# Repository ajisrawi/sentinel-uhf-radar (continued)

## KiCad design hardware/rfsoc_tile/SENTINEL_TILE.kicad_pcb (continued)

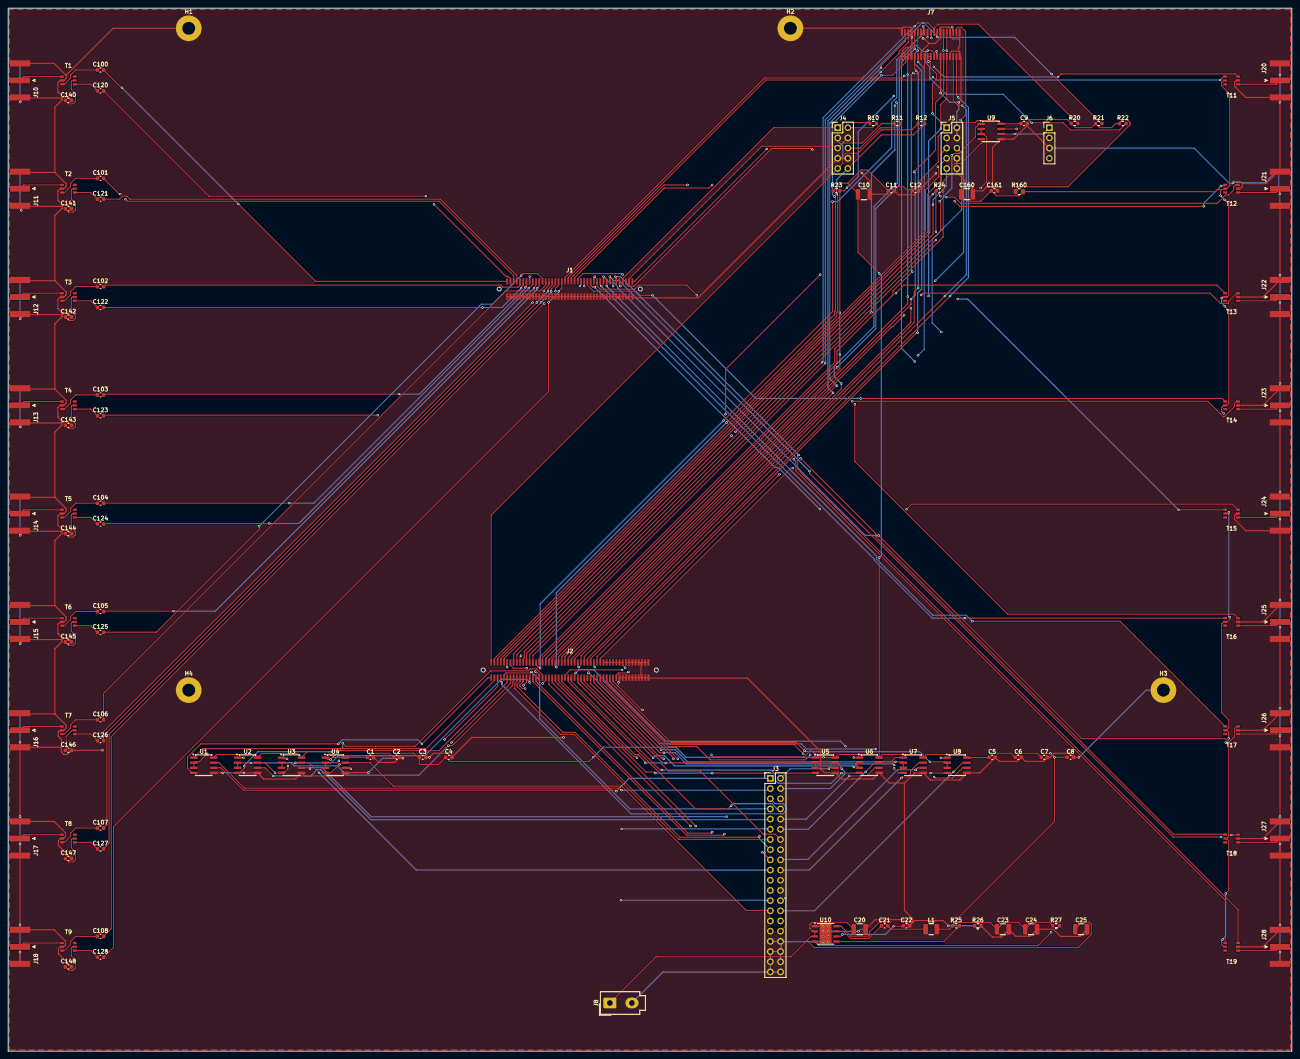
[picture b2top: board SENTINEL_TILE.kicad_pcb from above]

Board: 4 copper layers, 320.0 x 260.0 mm, 118 parts (0 on the bottom side), 187 nets.

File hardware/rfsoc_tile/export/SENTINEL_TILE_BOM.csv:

"Item","References","Qty","Value","Footprint","Description","MPN / part class"
"1","C1-C9,C11,C12,C21,C100-C108,C120-C128,C140-C148,C161","40","100n","Capacitor_SMD:C_0603_1608Metric","Centre-tap AC ground",""
"2","C10,C160","2","10u","Capacitor_SMD:C_1210_3225Metric","QSFP supply filter",""
"3","C20","1","10u 25V","Capacitor_SMD:C_1210_3225Metric","",""
"4","C22","1","1u","Capacitor_SMD:C_0603_1608Metric","",""
"5","C23,C24","2","22u","Capacitor_SMD:C_1210_3225Metric","",""
"6","C25","1","22u 25V","Capacitor_SMD:C_1210_3225Metric","",""
"7","H1-H4","4","M3","MountingHole:MountingHole_3.2mm_M3_Pad","",""
"8","J1","1","SOM CONN A","SENTINEL:SOM_B2B_2x40_P0.8","SOM data-converter connector",""
"9","J2","1","SOM CONN B","SENTINEL:SOM_B2B_2x50_P0.8","SOM control / optics / power connector",""
"10","J3","1","BACKPLANE","Connector_PinHeader_2.54mm:PinHeader_2x20_P2.54mm_Vertical","Cable to tile backplane J9 (pin-for-pin)",""
"11","J4","1","CLOCK","Connector_PinHeader_2.54mm:PinHeader_2x05_P2.54mm_Vertical","From clock board",""
"12","J5","1","CAL CTRL","Connector_PinHeader_2.54mm:PinHeader_2x05_P2.54mm_Vertical","To calibration board J11",""
"13","J6","1","PSU LINK","Connector_PinHeader_2.54mm:PinHeader_1x04_P2.54mm_Vertical","",""
"14","J7","1","QSFP28","SENTINEL:QSFP28_Host_38P","QSFP28 to face beamformer, 4 x 25 Gb/s",""
"15","J8","1","12V IN","Connector_Molex:Molex_Mini-Fit_Jr_5566-02A_2x01_P4.20mm_Vertical","12 V from subarray PSU aux, 4 A",""
"16","J10","1","RX1","Connector_Coaxial:SMA_Amphenol_132289_EdgeMount","From T/R module 1 RX_OUT",""
"17","J11","1","RX2","Connector_Coaxial:SMA_Amphenol_132289_EdgeMount","From T/R module 2 RX_OUT",""
"18","J12","1","RX3","Connector_Coaxial:SMA_Amphenol_132289_EdgeMount","From T/R module 3 RX_OUT",""
"19","J13","1","RX4","Connector_Coaxial:SMA_Amphenol_132289_EdgeMount","From T/R module 4 RX_OUT",""
"20","J14","1","RX5","Connector_Coaxial:SMA_Amphenol_132289_EdgeMount","From T/R module 5 RX_OUT",""
"21","J15","1","RX6","Connector_Coaxial:SMA_Amphenol_132289_EdgeMount","From T/R module 6 RX_OUT",""
"22","J16","1","RX7","Connector_Coaxial:SMA_Amphenol_132289_EdgeMount","From T/R module 7 RX_OUT",""
"23","J17","1","RX8","Connector_Coaxial:SMA_Amphenol_132289_EdgeMount","From T/R module 8 RX_OUT",""
"24","J18","1","RXCAL","Connector_Coaxial:SMA_Amphenol_132289_EdgeMount","From calibration board MEASURE",""
"25","J20","1","TX1","Connector_Coaxial:SMA_Amphenol_132289_EdgeMount","To T/R module 1 TX_IN",""
"26","J21","1","TX2","Connector_Coaxial:SMA_Amphenol_132289_EdgeMount","To T/R module 2 TX_IN",""
"27","J22","1","TX3","Connector_Coaxial:SMA_Amphenol_132289_EdgeMount","To T/R module 3 TX_IN",""
"28","J23","1","TX4","Connector_Coaxial:SMA_Amphenol_132289_EdgeMount","To T/R module 4 TX_IN",""
"29","J24","1","TX5","Connector_Coaxial:SMA_Amphenol_132289_EdgeMount","To T/R module 5 TX_IN",""
"30","J25","1","TX6","Connector_Coaxial:SMA_Amphenol_132289_EdgeMount","To T/R module 6 TX_IN",""
"31","J26","1","TX7","Connector_Coaxial:SMA_Amphenol_132289_EdgeMount","To T/R module 7 TX_IN",""
"32","J27","1","TX8","Connector_Coaxial:SMA_Amphenol_132289_EdgeMount","To T/R module 8 TX_IN",""
"33","J28","1","TXCAL","Connector_Coaxial:SMA_Amphenol_132289_EdgeMount","To calibration board INJECT",""
"34","L1","1","4.7u","Inductor_SMD:L_1210_3225Metric","",""
"35","R10-R12,R24","4","100","Resistor_SMD:R_0603_1608Metric","LVDS receiver termination,LVDS termination (DNP if SOM terminates),MGT reference clock termination (refclk from SOM oscillator)",""
"36","R20-R23","4","4.7k","Resistor_SMD:R_0603_1608Metric","",""
"37","R25,R27","2","100k","Resistor_SMD:R_0603_1608Metric","",""
"38","R26","1","43.2k","Resistor_SMD:R_0603_1608Metric","",""
"39","R160","1","0","Resistor_SMD:R_0805_2012Metric","DAC_AVTT from 3.3 V (fit per SOM DAC mode: 2.5 V or 3.0 V)",""
"40","T1-T9,T11-T19","18","1:2","SENTINEL:Balun_SMD_6P_3.8x3.8","ADC input transformer, 50 -> 100 ohm,DAC output transformer, centre tap biases the DAC",""
"41","U1-U9","9","THVD1450","Package_SO:SOIC-8_3.9x4.9mm_P1.27mm","RS-485 to T/R module 1,RS-485 to T/R module 2,RS-485 to T/R module 3,RS-485 to T/R module 4,RS-485 to T/R module 5,RS-485 to T/R module 6,RS-485 to T/R module 7,RS-485 to T/R module 8,RS-485 to subarray PSU",""
"42","U10","1","LMR33630","Package_SO:Texas_HSOP-8-1EP_3.9x4.9mm_P1.27mm_ThermalVias","12 V -> 3.3 V, 3 A",""

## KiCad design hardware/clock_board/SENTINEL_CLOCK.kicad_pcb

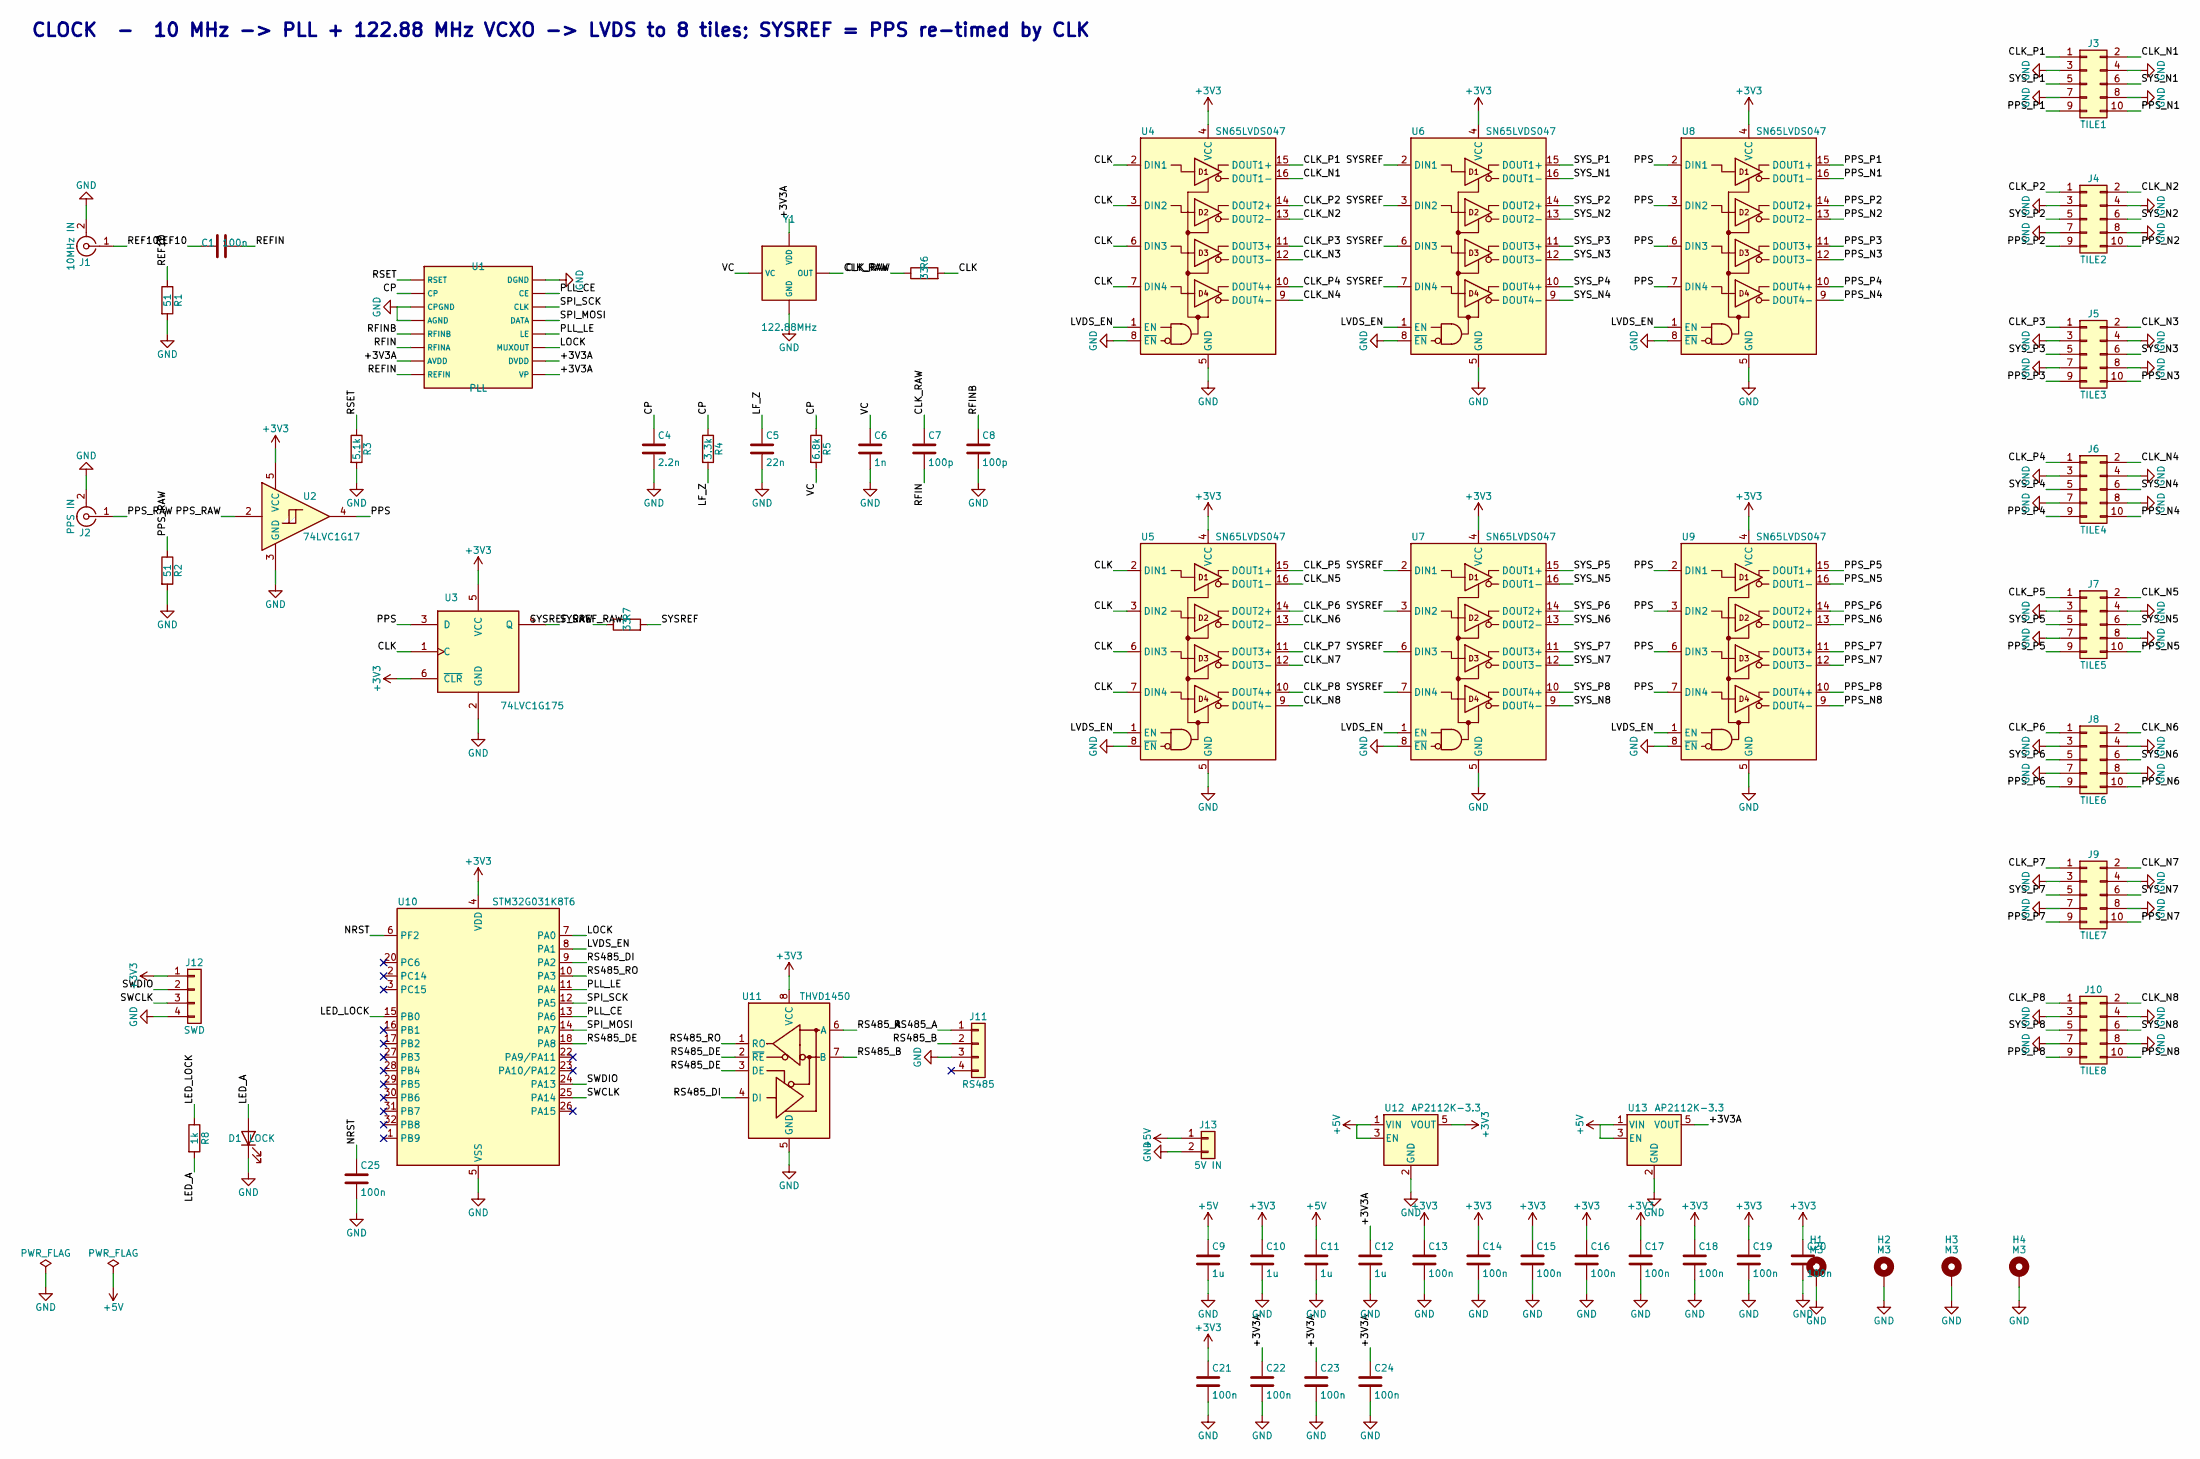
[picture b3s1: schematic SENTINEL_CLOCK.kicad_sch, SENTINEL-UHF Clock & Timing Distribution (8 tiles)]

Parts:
C1, C13, C14, C15, C16, C17, C18, C19, C20, C21, C22, C23, C24, C25: 100n; C_0603_1608Metric
C4: 2.2n; C_0603_1608Metric
C5: 22n; C_0603_1608Metric
C6: 1n; C_0603_1608Metric
C7, C8: 100p; C_0603_1608Metric
C9, C10, C11, C12: 1u; C_0603_1608Metric
D1: LOCK; LED_0603_1608Metric
H1, H2, H3, H4: M3; MountingHole_3.2mm_M3_Pad
J1: 10MHz IN; SMA_Amphenol_132289_EdgeMount
J2: PPS IN; SMA_Amphenol_132289_EdgeMount
J3: TILE1; PinHeader_2x05_P2.54mm_Vertical
J4: TILE2; PinHeader_2x05_P2.54mm_Vertical
J5: TILE3; PinHeader_2x05_P2.54mm_Vertical
J6: TILE4; PinHeader_2x05_P2.54mm_Vertical
J7: TILE5; PinHeader_2x05_P2.54mm_Vertical
J8: TILE6; PinHeader_2x05_P2.54mm_Vertical
J9: TILE7; PinHeader_2x05_P2.54mm_Vertical
J10: TILE8; PinHeader_2x05_P2.54mm_Vertical
J11: RS485; PinHeader_1x04_P2.54mm_Vertical
J12: SWD; PinHeader_1x04_P2.54mm_Vertical
J13: 5V IN; Molex_Mini-Fit_Jr_5566-02A_2x01_P4.20mm_Vertical
R1, R2: 51; R_0603_1608Metric
R3: 5.1k; R_0603_1608Metric
R4: 3.3k; R_0603_1608Metric
R5: 6.8k; R_0603_1608Metric
R6, R7: 33; R_0603_1608Metric
R8: 1k; R_0603_1608Metric
U1: PLL; TSSOP-16_4.4x5mm_P0.65mm
U2: 74LVC1G17; SOT-23-5
U3: 74LVC1G175; SOT-363_SC-70-6
U4, U5, U6, U7, U8, U9: SN65LVDS047; SOIC-16_3.9x9.9mm_P1.27mm
U10: STM32G031K8T6; LQFP-32_7x7mm_P0.8mm
U11: THVD1450; SOIC-8_3.9x4.9mm_P1.27mm
U12, U13: AP2112K-3.3; SOT-23-5
Y1: 122.88MHz; Oscillator_SMD_EuroQuartz_XO53-4Pin_5.0x3.2mm

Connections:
+3V3: C10.1, C13.1, C14.1, C15.1, C16.1, C17.1, C18.1, C19.1, C20.1, C21.1, J12.1, U2.5 (VCC), U3.5 (VCC), U3.6 (~CLR), U4.4 (VCC), U5.4 (VCC), U6.4 (VCC), U7.4 (VCC), U8.4 (VCC), U9.4 (VCC), U10.4 (VDD), U11.8 (VCC), U12.5 (VOUT)
+3V3A: C12.1, C22.1, C23.1, C24.1, U1.7 (AVDD), U1.15 (DVDD), U1.16 (VP), U13.5 (VOUT), Y1.4 (VDD)
+5V: C9.1, C11.1, J13.1, U12.1 (VIN), U12.3 (EN), U13.1 (VIN), U13.3 (EN)
CLK: R6.2, U3.1 (C), U4.2 (DIN1), U4.3 (DIN2), U4.6 (DIN3), U4.7 (DIN4), U5.2 (DIN1), U5.3 (DIN2), U5.6 (DIN3), U5.7 (DIN4)
CLK_N1: J3.2, U4.16 (DOUT1-)
CLK_N2: J4.2, U4.13 (DOUT2-)
CLK_N3: J5.2, U4.12 (DOUT3-)
CLK_N4: J6.2, U4.9 (DOUT4-)
CLK_N5: J7.2, U5.16 (DOUT1-)
CLK_N6: J8.2, U5.13 (DOUT2-)
CLK_N7: J9.2, U5.12 (DOUT3-)
CLK_N8: J10.2, U5.9 (DOUT4-)
CLK_P1: J3.1, U4.15 (DOUT1+)
CLK_P2: J4.1, U4.14 (DOUT2+)
CLK_P3: J5.1, U4.11 (DOUT3+)
CLK_P4: J6.1, U4.10 (DOUT4+)
CLK_P5: J7.1, U5.15 (DOUT1+)
CLK_P6: J8.1, U5.14 (DOUT2+)
CLK_P7: J9.1, U5.11 (DOUT3+)
CLK_P8: J10.1, U5.10 (DOUT4+)
CLK_RAW: C7.1, R6.1, Y1.3 (OUT)
CP: C4.1, R4.1, R5.1, U1.2 (CP)
GND: C4.2, C5.2, C6.2, C8.2, C9.2, C10.2, C11.2, C12.2, C13.2, C14.2, C15.2, C16.2, C17.2, C18.2, C19.2, C20.2, C21.2, C22.2, C23.2, C24.2, C25.2, D1.1 (K), H1.1, H2.1, H3.1, H4.1, J1.2 (Ext), J2.2 (Ext), J3.3, J3.4, J3.7, J3.8, J4.3, J4.4, J4.7, J4.8, J5.3, J5.4, J5.7, J5.8, J6.3, J6.4, J6.7, J6.8, J7.3, J7.4, J7.7, J7.8, J8.3, J8.4, J8.7, J8.8, J9.3, J9.4, J9.7, J9.8, J10.3, J10.4, J10.7, J10.8, J11.3, J12.4, J13.2, R1.2, R2.2, R3.2, U1.3 (CPGND), U1.4 (AGND), U1.9 (DGND), U2.3 (GND), U3.2 (GND), U4.5 (GND), U4.8 (~EN), U5.5 (GND), U5.8 (~EN), U6.5 (GND), U6.8 (~EN), U7.5 (GND), U7.8 (~EN), U8.5 (GND), U8.8 (~EN), U9.5 (GND), U9.8 (~EN), U10.5 (VSS), U11.5 (GND), U12.2 (GND), U13.2 (GND), Y1.2 (GND)
LED_A: D1.2 (A), R8.2
LED_LOCK: R8.1, U10.15 (PB0)
LF_Z: C5.1, R4.2
LOCK: U1.14 (MUXOUT), U10.7 (PA0)
LVDS_EN: U4.1 (EN), U5.1 (EN), U6.1 (EN), U7.1 (EN), U8.1 (EN), U9.1 (EN), U10.8 (PA1)
NRST: C25.1, U10.6 (PF2)
PLL_CE: U1.10 (CE), U10.13 (PA6)
PLL_LE: U1.13 (LE), U10.11 (PA4)
PPS: U2.4, U3.3 (D), U8.2 (DIN1), U8.3 (DIN2), U8.6 (DIN3), U8.7 (DIN4), U9.2 (DIN1), U9.3 (DIN2), U9.6 (DIN3), U9.7 (DIN4)
PPS_N1: J3.10, U8.16 (DOUT1-)
PPS_N2: J4.10, U8.13 (DOUT2-)
PPS_N3: J5.10, U8.12 (DOUT3-)
PPS_N4: J6.10, U8.9 (DOUT4-)
PPS_N5: J7.10, U9.16 (DOUT1-)
PPS_N6: J8.10, U9.13 (DOUT2-)
PPS_N7: J9.10, U9.12 (DOUT3-)
PPS_N8: J10.10, U9.9 (DOUT4-)
PPS_P1: J3.9, U8.15 (DOUT1+)
PPS_P2: J4.9, U8.14 (DOUT2+)
PPS_P3: J5.9, U8.11 (DOUT3+)
PPS_P4: J6.9, U8.10 (DOUT4+)
PPS_P5: J7.9, U9.15 (DOUT1+)
PPS_P6: J8.9, U9.14 (DOUT2+)
PPS_P7: J9.9, U9.11 (DOUT3+)
PPS_P8: J10.9, U9.10 (DOUT4+)
PPS_RAW: J2.1 (In), R2.1, U2.2
REF10: C1.1, J1.1 (In), R1.1
REFIN: C1.2, U1.8 (REFIN)
RFIN: C7.2, U1.6 (RFINA)
RFINB: C8.1, U1.5 (RFINB)
RS485_A: J11.1, U11.6 (A)
RS485_B: J11.2, U11.7 (B)
RS485_DE: U10.18 (PA8), U11.2 (~RE), U11.3 (DE)
RS485_DI: U10.9 (PA2), U11.4 (DI)
RS485_RO: U10.10 (PA3), U11.1 (RO)
RSET: R3.1, U1.1 (RSET)
SPI_MOSI: U1.12 (DATA), U10.14 (PA7)
SPI_SCK: U1.11 (CLK), U10.12 (PA5)
SWCLK: J12.3, U10.25 (PA14)
SWDIO: J12.2, U10.24 (PA13)
SYSREF: R7.2, U6.2 (DIN1), U6.3 (DIN2), U6.6 (DIN3), U6.7 (DIN4), U7.2 (DIN1), U7.3 (DIN2), U7.6 (DIN3), U7.7 (DIN4)
SYSREF_RAW: R7.1, U3.4 (Q)
SYS_N1: J3.6, U6.16 (DOUT1-)
SYS_N2: J4.6, U6.13 (DOUT2-)
SYS_N3: J5.6, U6.12 (DOUT3-)
SYS_N4: J6.6, U6.9 (DOUT4-)
SYS_N5: J7.6, U7.16 (DOUT1-)
SYS_N6: J8.6, U7.13 (DOUT2-)
SYS_N7: J9.6, U7.12 (DOUT3-)
SYS_N8: J10.6, U7.9 (DOUT4-)
SYS_P1: J3.5, U6.15 (DOUT1+)
SYS_P2: J4.5, U6.14 (DOUT2+)
SYS_P3: J5.5, U6.11 (DOUT3+)
SYS_P4: J6.5, U6.10 (DOUT4+)
SYS_P5: J7.5, U7.15 (DOUT1+)
SYS_P6: J8.5, U7.14 (DOUT2+)
SYS_P7: J9.5, U7.11 (DOUT3+)
SYS_P8: J10.5, U7.10 (DOUT4+)
VC: C6.1, R5.2, Y1.1 (VC)

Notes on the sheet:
CLOCK - 10 MHz -> PLL + 122.88 MHz VCXO -> LVDS to 8 tiles; SYSREF = PPS re-timed by CLK

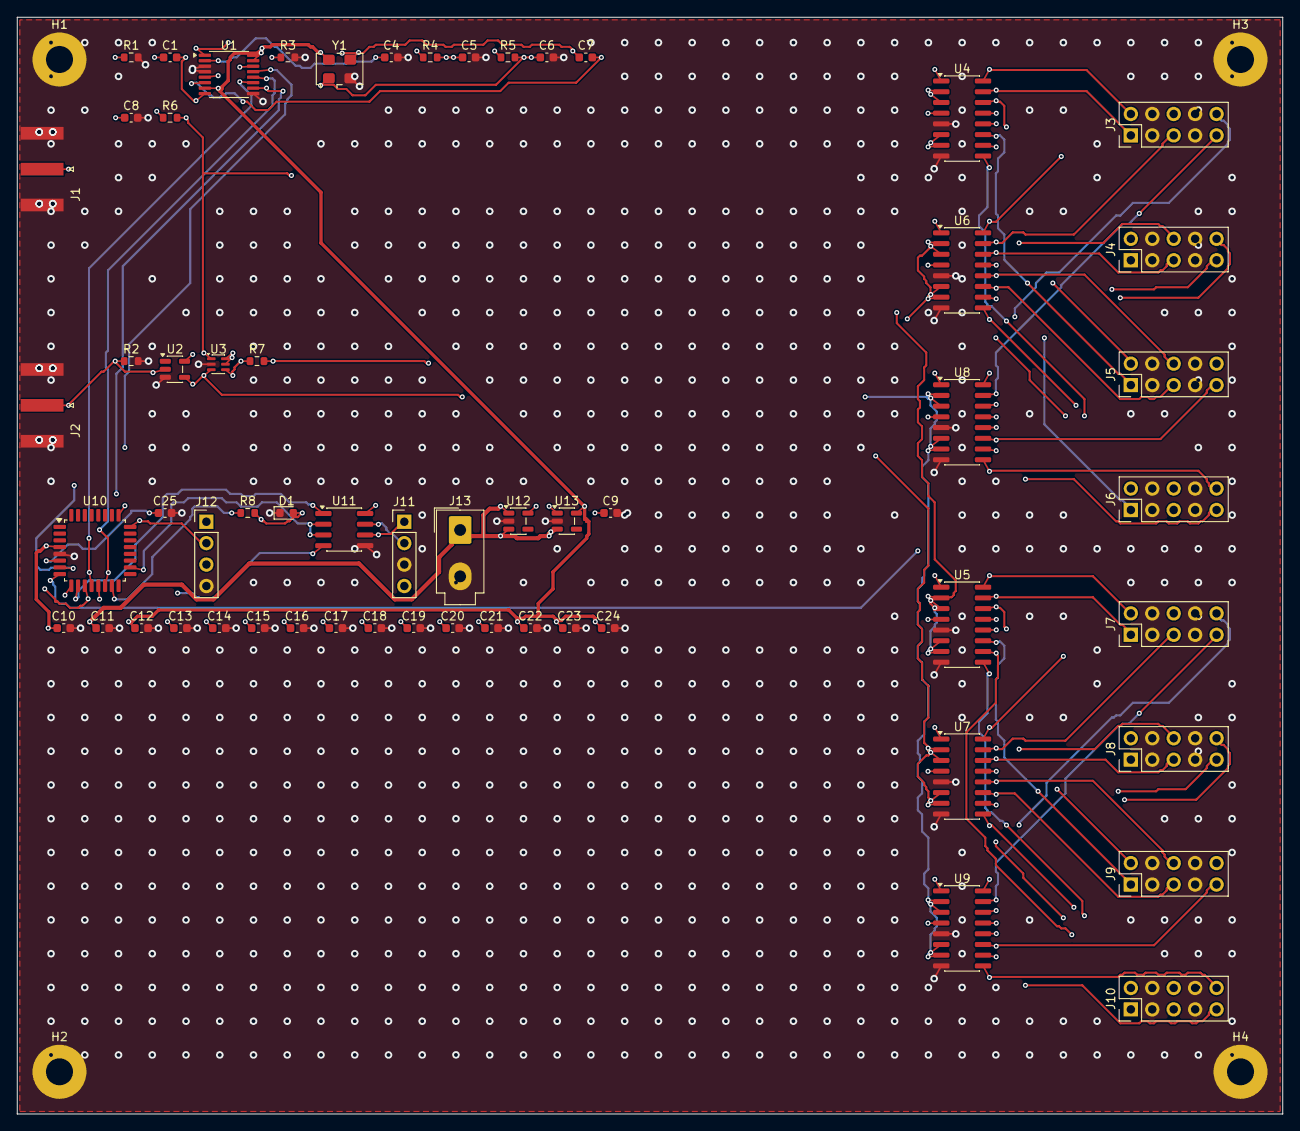
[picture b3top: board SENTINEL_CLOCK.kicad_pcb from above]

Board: 4 copper layers, 150.0 x 130.0 mm, 63 parts (0 on the bottom side), 82 nets.

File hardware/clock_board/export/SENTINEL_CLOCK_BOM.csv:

"Item","References","Qty","Value","Footprint","Description","MPN / part class"
"1","C1,C13-C25","14","100n","Capacitor_SMD:C_0603_1608Metric","",""
"2","C4","1","2.2n","Capacitor_SMD:C_0603_1608Metric","Loop filter (100 Hz loop)",""
"3","C5","1","22n","Capacitor_SMD:C_0603_1608Metric","Loop filter (100 Hz loop)",""
"4","C6","1","1n","Capacitor_SMD:C_0603_1608Metric","Loop filter (100 Hz loop)",""
"5","C7,C8","2","100p","Capacitor_SMD:C_0603_1608Metric","",""
"6","C9-C12","4","1u","Capacitor_SMD:C_0603_1608Metric","",""
"7","D1","1","LOCK","LED_SMD:LED_0603_1608Metric","",""
"8","H1-H4","4","M3","MountingHole:MountingHole_3.2mm_M3_Pad","",""
"9","J1","1","10MHz IN","Connector_Coaxial:SMA_Amphenol_132289_EdgeMount","10 MHz from site master, +7 dBm sine",""
"10","J2","1","PPS IN","Connector_Coaxial:SMA_Amphenol_132289_EdgeMount","1 PPS from site master",""
"11","J3","1","TILE1","Connector_PinHeader_2.54mm:PinHeader_2x05_P2.54mm_Vertical","Clock bundle to tile 1",""
"12","J4","1","TILE2","Connector_PinHeader_2.54mm:PinHeader_2x05_P2.54mm_Vertical","Clock bundle to tile 2",""
"13","J5","1","TILE3","Connector_PinHeader_2.54mm:PinHeader_2x05_P2.54mm_Vertical","Clock bundle to tile 3",""
"14","J6","1","TILE4","Connector_PinHeader_2.54mm:PinHeader_2x05_P2.54mm_Vertical","Clock bundle to tile 4",""
"15","J7","1","TILE5","Connector_PinHeader_2.54mm:PinHeader_2x05_P2.54mm_Vertical","Clock bundle to tile 5",""
"16","J8","1","TILE6","Connector_PinHeader_2.54mm:PinHeader_2x05_P2.54mm_Vertical","Clock bundle to tile 6",""
"17","J9","1","TILE7","Connector_PinHeader_2.54mm:PinHeader_2x05_P2.54mm_Vertical","Clock bundle to tile 7",""
"18","J10","1","TILE8","Connector_PinHeader_2.54mm:PinHeader_2x05_P2.54mm_Vertical","Clock bundle to tile 8",""
"19","J11","1","RS485","Connector_PinHeader_2.54mm:PinHeader_1x04_P2.54mm_Vertical","To site timing controller",""
"20","J12","1","SWD","Connector_PinHeader_2.54mm:PinHeader_1x04_P2.54mm_Vertical","",""
"21","J13","1","5V IN","Connector_Molex:Molex_Mini-Fit_Jr_5566-02A_2x01_P4.20mm_Vertical","",""
"22","R1,R2","2","51","Resistor_SMD:R_0603_1608Metric","50 ohm termination",""
"23","R3","1","5.1k","Resistor_SMD:R_0603_1608Metric","",""
"24","R4","1","3.3k","Resistor_SMD:R_0603_1608Metric","Loop filter (100 Hz loop)",""
"25","R5","1","6.8k","Resistor_SMD:R_0603_1608Metric","Loop filter (100 Hz loop)",""
"26","R6,R7","2","33","Resistor_SMD:R_0603_1608Metric","Source termination",""
"27","R8","1","1k","Resistor_SMD:R_0603_1608Metric","",""
"28","U1","1","PLL","Package_SO:TSSOP-16_4.4x5mm_P0.65mm","Integer-N PLL, verify pin map",""
"29","U2","1","74LVC1G17","Package_TO_SOT_SMD:SOT-23-5","PPS Schmitt buffer",""
"30","U3","1","74LVC1G175","Package_TO_SOT_SMD:SOT-363_SC-70-6","SYSREF: PPS re-timed by CLK",""
"31","U4-U9","6","SN65LVDS047","Package_SO:SOIC-16_3.9x9.9mm_P1.27mm","Quad LVDS driver, CLK to tiles 1-4,Quad LVDS driver, CLK to tiles 5-8,Quad LVDS driver, PPS to tiles 1-4,Quad LVDS driver, PPS to tiles 5-8,Quad LVDS driver, SYSREF to tiles 1-4,Quad LVDS driver, SYSREF to tiles 5-8",""
"32","U10","1","STM32G031K8T6","Package_QFP:LQFP-32_7x7mm_P0.8mm","Programs the PLL, reports lock, enables outputs",""
"33","U11","1","THVD1450","Package_SO:SOIC-8_3.9x4.9mm_P1.27mm","",""
"34","U12,U13","2","AP2112K-3.3","Package_TO_SOT_SMD:SOT-23-5","Analog rail for PLL/VCXO",""
"35","Y1","1","122.88MHz","Oscillator:Oscillator_SMD_EuroQuartz_XO53-4Pin_5.0x3.2mm","122.88 MHz VCXO, low phase noise",""

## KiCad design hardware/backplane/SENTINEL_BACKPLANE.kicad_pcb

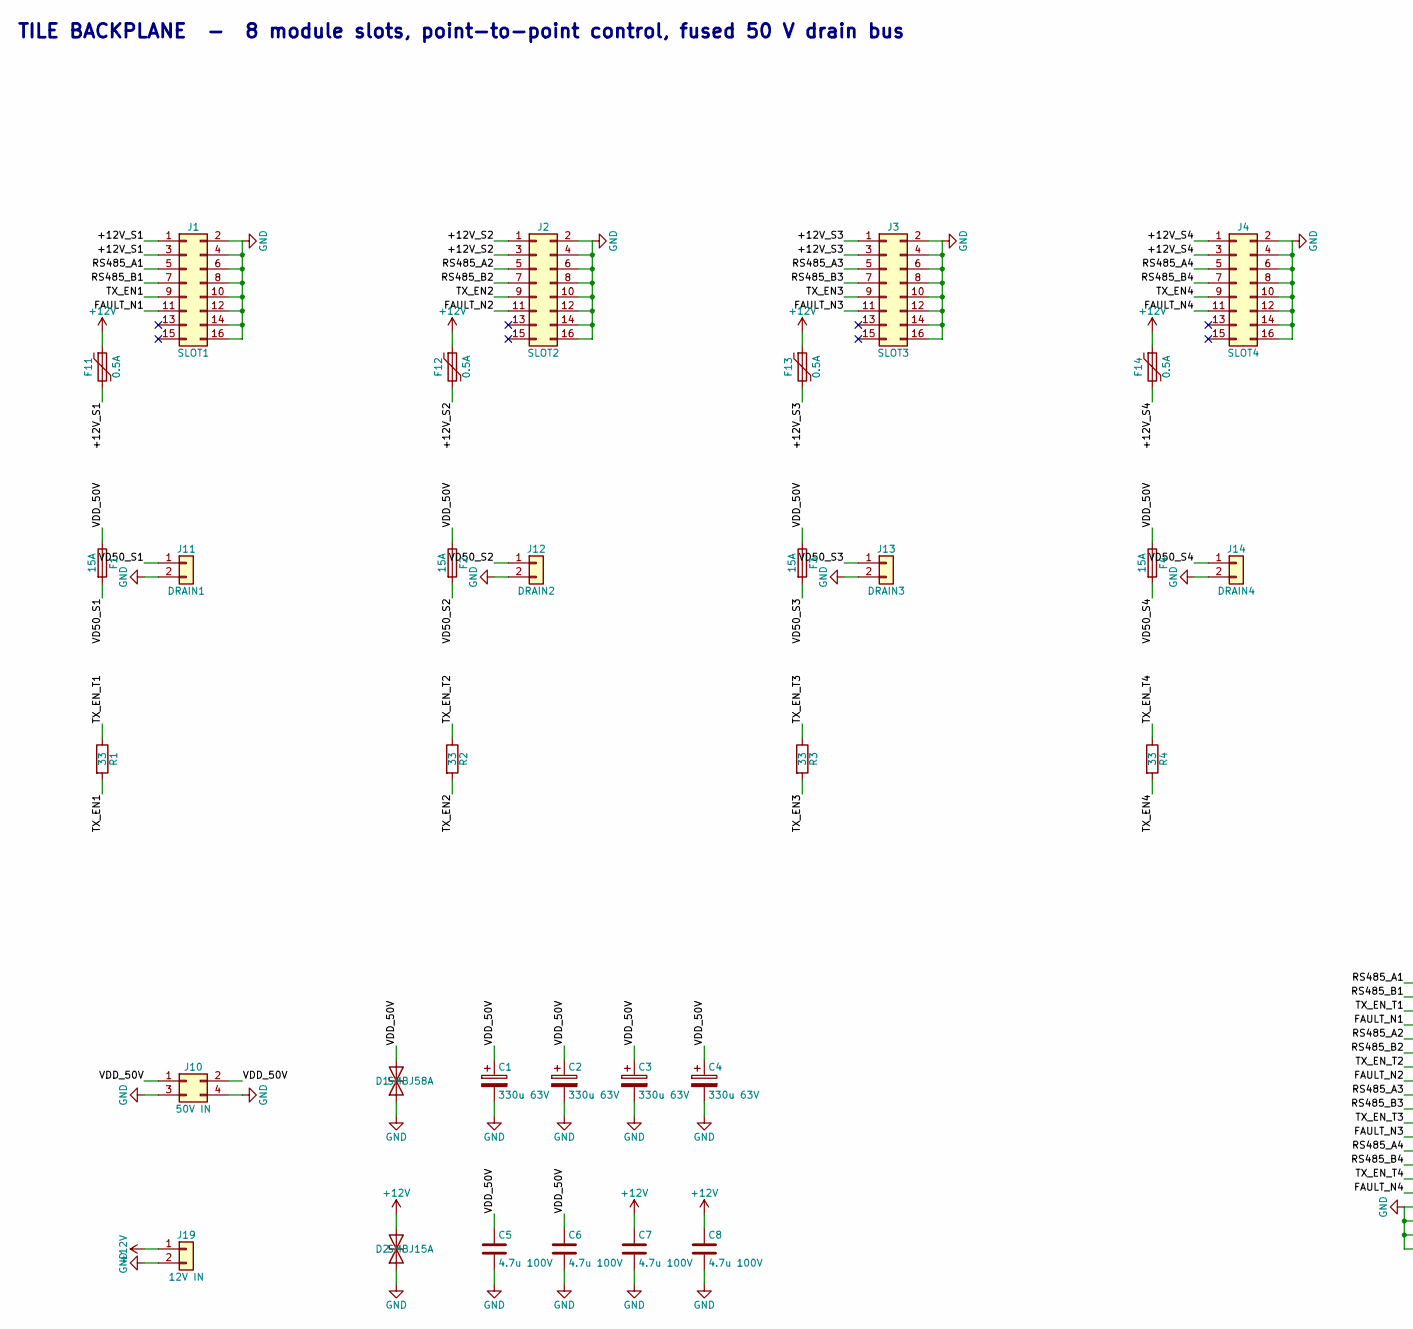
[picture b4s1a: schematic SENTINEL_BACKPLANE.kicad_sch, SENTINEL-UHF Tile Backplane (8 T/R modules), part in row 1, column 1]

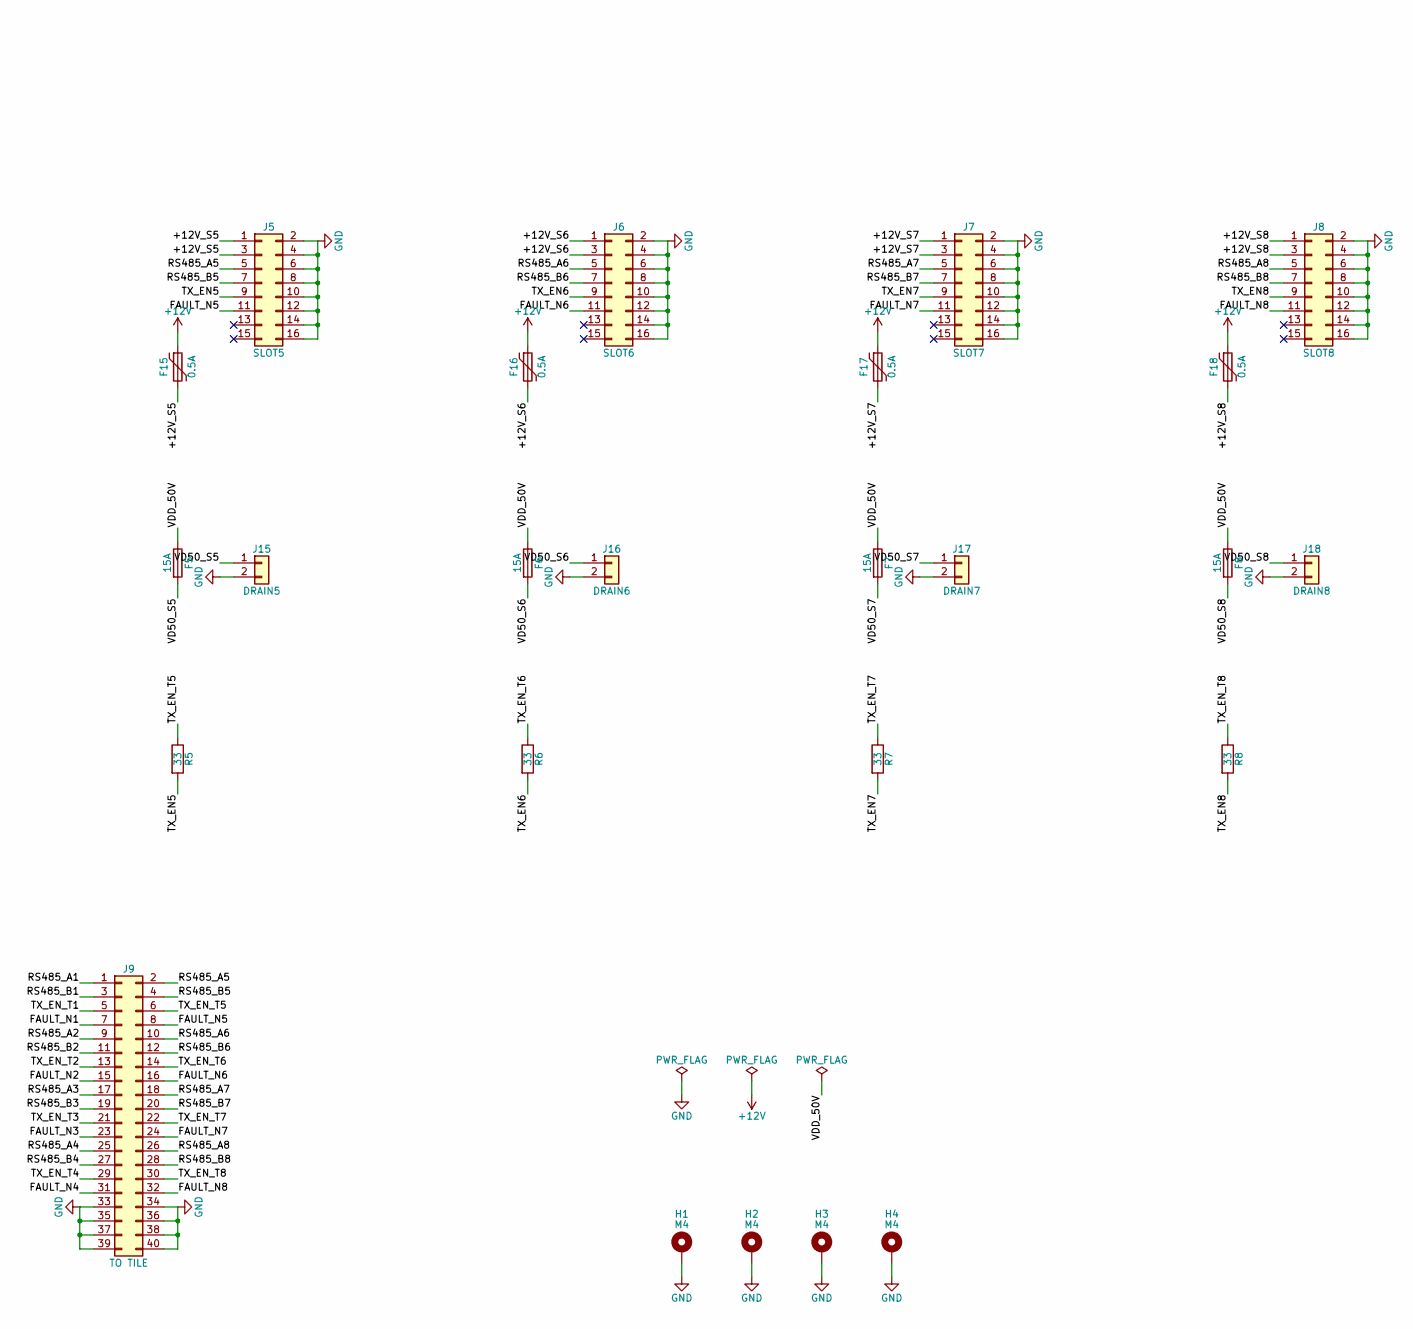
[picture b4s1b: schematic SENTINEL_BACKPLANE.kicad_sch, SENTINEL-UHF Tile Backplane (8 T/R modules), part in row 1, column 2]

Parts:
C1, C2, C3, C4: 330u 63V; CP_Elec_10x10.5
C5, C6, C7, C8: 4.7u 100V; C_1210_3225Metric
D1: SMBJ58A; D_SMB
D2: SMBJ15A; D_SMB
F1, F2, F3, F4, F5, F6, F7, F8: 15A; Fuse_456_SMD
F11, F12, F13, F14, F15, F16, F17, F18: 0.5A; Fuse_1812_4532Metric
H1, H2, H3, H4: M4; MountingHole_3.2mm_M3_Pad
J1: SLOT1; PinHeader_2x08_P2.54mm_Vertical
J2: SLOT2; PinHeader_2x08_P2.54mm_Vertical
J3: SLOT3; PinHeader_2x08_P2.54mm_Vertical
J4: SLOT4; PinHeader_2x08_P2.54mm_Vertical
J5: SLOT5; PinHeader_2x08_P2.54mm_Vertical
J6: SLOT6; PinHeader_2x08_P2.54mm_Vertical
J7: SLOT7; PinHeader_2x08_P2.54mm_Vertical
J8: SLOT8; PinHeader_2x08_P2.54mm_Vertical
J9: TO TILE; PinHeader_2x20_P2.54mm_Vertical
J10: 50V IN; Molex_Mini-Fit_Jr_5566-04A_2x02_P4.20mm_Vertical
J11: DRAIN1; Molex_Mini-Fit_Jr_5566-02A_2x01_P4.20mm_Vertical
J12: DRAIN2; Molex_Mini-Fit_Jr_5566-02A_2x01_P4.20mm_Vertical
J13: DRAIN3; Molex_Mini-Fit_Jr_5566-02A_2x01_P4.20mm_Vertical
J14: DRAIN4; Molex_Mini-Fit_Jr_5566-02A_2x01_P4.20mm_Vertical
J15: DRAIN5; Molex_Mini-Fit_Jr_5566-02A_2x01_P4.20mm_Vertical
J16: DRAIN6; Molex_Mini-Fit_Jr_5566-02A_2x01_P4.20mm_Vertical
J17: DRAIN7; Molex_Mini-Fit_Jr_5566-02A_2x01_P4.20mm_Vertical
J18: DRAIN8; Molex_Mini-Fit_Jr_5566-02A_2x01_P4.20mm_Vertical
J19: 12V IN; Molex_Mini-Fit_Jr_5566-02A_2x01_P4.20mm_Vertical
R1, R2, R3, R4, R5, R6, R7, R8: 33; R_0603_1608Metric

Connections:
+12V: C7.1, C8.1, D2.2 (A2), F11.1, F12.1, F13.1, F14.1, F15.1, F16.1, F17.1, F18.1, J19.1
+12V_S1: F11.2, J1.1, J1.3
+12V_S2: F12.2, J2.1, J2.3
+12V_S3: F13.2, J3.1, J3.3
+12V_S4: F14.2, J4.1, J4.3
+12V_S5: F15.2, J5.1, J5.3
+12V_S6: F16.2, J6.1, J6.3
+12V_S7: F17.2, J7.1, J7.3
+12V_S8: F18.2, J8.1, J8.3
FAULT_N1: J1.11, J9.7
FAULT_N2: J2.11, J9.15
FAULT_N3: J3.11, J9.23
FAULT_N4: J4.11, J9.31
FAULT_N5: J5.11, J9.8
FAULT_N6: J6.11, J9.16
FAULT_N7: J7.11, J9.24
FAULT_N8: J8.11, J9.32
GND: C1.2, C2.2, C3.2, C4.2, C5.2, C6.2, C7.2, C8.2, D1.1 (A1), D2.1 (A1), H1.1, H2.1, H3.1, H4.1, J1.2, J1.4, J1.6, J1.8, J1.10, J1.12, J1.14, J1.16, J2.2, J2.4, J2.6, J2.8, J2.10, J2.12, J2.14, J2.16, J3.2, J3.4, J3.6, J3.8, J3.10, J3.12, J3.14, J3.16, J4.2, J4.4, J4.6, J4.8, J4.10, J4.12, J4.14, J4.16, J5.2, J5.4, J5.6, J5.8, J5.10, J5.12, J5.14, J5.16, J6.2, J6.4, J6.6, J6.8, J6.10, J6.12, J6.14, J6.16, J7.2, J7.4, J7.6, J7.8, J7.10, J7.12, J7.14, J7.16, J8.2, J8.4, J8.6, J8.8, J8.10, J8.12, J8.14, J8.16, J9.33, J9.34, J9.35, J9.36, J9.37, J9.38, J9.39, J9.40, J10.3, J10.4, J11.2, J12.2, J13.2, J14.2, J15.2, J16.2, J17.2, J18.2, J19.2
RS485_A1: J1.5, J9.1
RS485_A2: J2.5, J9.9
RS485_A3: J3.5, J9.17
RS485_A4: J4.5, J9.25
RS485_A5: J5.5, J9.2
RS485_A6: J6.5, J9.10
RS485_A7: J7.5, J9.18
RS485_A8: J8.5, J9.26
RS485_B1: J1.7, J9.3
RS485_B2: J2.7, J9.11
RS485_B3: J3.7, J9.19
RS485_B4: J4.7, J9.27
RS485_B5: J5.7, J9.4
RS485_B6: J6.7, J9.12
RS485_B7: J7.7, J9.20
RS485_B8: J8.7, J9.28
TX_EN1: J1.9, R1.2
TX_EN2: J2.9, R2.2
TX_EN3: J3.9, R3.2
TX_EN4: J4.9, R4.2
TX_EN5: J5.9, R5.2
TX_EN6: J6.9, R6.2
TX_EN7: J7.9, R7.2
TX_EN8: J8.9, R8.2
TX_EN_T1: J9.5, R1.1
TX_EN_T2: J9.13, R2.1
TX_EN_T3: J9.21, R3.1
TX_EN_T4: J9.29, R4.1
TX_EN_T5: J9.6, R5.1
TX_EN_T6: J9.14, R6.1
TX_EN_T7: J9.22, R7.1
TX_EN_T8: J9.30, R8.1
VD50_S1: F1.2, J11.1
VD50_S2: F2.2, J12.1
VD50_S3: F3.2, J13.1
VD50_S4: F4.2, J14.1
VD50_S5: F5.2, J15.1
VD50_S6: F6.2, J16.1
VD50_S7: F7.2, J17.1
VD50_S8: F8.2, J18.1
VDD_50V: C1.1, C2.1, C3.1, C4.1, C5.1, C6.1, D1.2 (A2), F1.1, F2.1, F3.1, F4.1, F5.1, F6.1, F7.1, F8.1, J10.1, J10.2

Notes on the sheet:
TILE BACKPLANE - 8 module slots, point-to-point control, fused 50 V drain bus

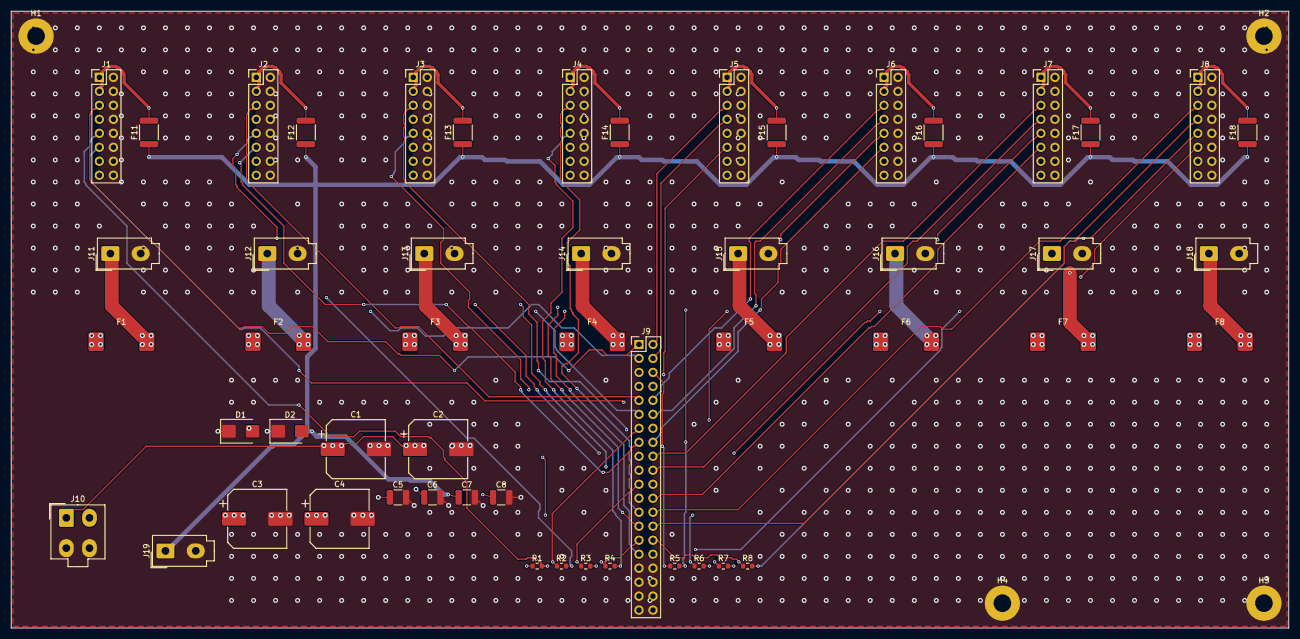
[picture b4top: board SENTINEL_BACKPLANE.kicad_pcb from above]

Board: 4 copper layers, 232.0 x 112.0 mm, 57 parts (0 on the bottom side), 59 nets.

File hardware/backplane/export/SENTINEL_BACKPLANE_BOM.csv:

"Item","References","Qty","Value","Footprint","Description","MPN / part class"
"1","C1-C4","4","330u 63V","Capacitor_SMD:CP_Elec_10x10.5","Bus reservoir",""
"2","C5-C8","4","4.7u 100V","Capacitor_SMD:C_1210_3225Metric","",""
"3","D1","1","SMBJ58A","Diode_SMD:D_SMB","",""
"4","D2","1","SMBJ15A","Diode_SMD:D_SMB","",""
"5","F1-F8","8","15A","SENTINEL:Fuse_456_SMD","15 A fast fuse, per-slot drain protection",""
"6","F11-F18","8","0.5A","Fuse:Fuse_1812_4532Metric","Resettable fuse, module aux power",""
"7","H1-H4","4","M4","MountingHole:MountingHole_3.2mm_M3_Pad","",""
"8","J1","1","SLOT1","Connector_PinHeader_2.54mm:PinHeader_2x08_P2.54mm_Vertical","T/R module 1 control header (mates module J5)",""
"9","J2","1","SLOT2","Connector_PinHeader_2.54mm:PinHeader_2x08_P2.54mm_Vertical","T/R module 2 control header (mates module J5)",""
"10","J3","1","SLOT3","Connector_PinHeader_2.54mm:PinHeader_2x08_P2.54mm_Vertical","T/R module 3 control header (mates module J5)",""
"11","J4","1","SLOT4","Connector_PinHeader_2.54mm:PinHeader_2x08_P2.54mm_Vertical","T/R module 4 control header (mates module J5)",""
"12","J5","1","SLOT5","Connector_PinHeader_2.54mm:PinHeader_2x08_P2.54mm_Vertical","T/R module 5 control header (mates module J5)",""
"13","J6","1","SLOT6","Connector_PinHeader_2.54mm:PinHeader_2x08_P2.54mm_Vertical","T/R module 6 control header (mates module J5)",""
"14","J7","1","SLOT7","Connector_PinHeader_2.54mm:PinHeader_2x08_P2.54mm_Vertical","T/R module 7 control header (mates module J5)",""
"15","J8","1","SLOT8","Connector_PinHeader_2.54mm:PinHeader_2x08_P2.54mm_Vertical","T/R module 8 control header (mates module J5)",""
"16","J9","1","TO TILE","Connector_PinHeader_2.54mm:PinHeader_2x20_P2.54mm_Vertical","To RFSoC tile: 8 x (RS-485 A/B, TX_EN, FAULT_N)",""
"17","J10","1","50V IN","Connector_Molex:Molex_Mini-Fit_Jr_5566-04A_2x02_P4.20mm_Vertical","50 V from subarray supply, 40 A pk",""
"18","J11","1","DRAIN1","Connector_Molex:Molex_Mini-Fit_Jr_5566-02A_2x01_P4.20mm_Vertical","Module 1 50 V drain feed",""
"19","J12","1","DRAIN2","Connector_Molex:Molex_Mini-Fit_Jr_5566-02A_2x01_P4.20mm_Vertical","Module 2 50 V drain feed",""
"20","J13","1","DRAIN3","Connector_Molex:Molex_Mini-Fit_Jr_5566-02A_2x01_P4.20mm_Vertical","Module 3 50 V drain feed",""
"21","J14","1","DRAIN4","Connector_Molex:Molex_Mini-Fit_Jr_5566-02A_2x01_P4.20mm_Vertical","Module 4 50 V drain feed",""
"22","J15","1","DRAIN5","Connector_Molex:Molex_Mini-Fit_Jr_5566-02A_2x01_P4.20mm_Vertical","Module 5 50 V drain feed",""
"23","J16","1","DRAIN6","Connector_Molex:Molex_Mini-Fit_Jr_5566-02A_2x01_P4.20mm_Vertical","Module 6 50 V drain feed",""
"24","J17","1","DRAIN7","Connector_Molex:Molex_Mini-Fit_Jr_5566-02A_2x01_P4.20mm_Vertical","Module 7 50 V drain feed",""
"25","J18","1","DRAIN8","Connector_Molex:Molex_Mini-Fit_Jr_5566-02A_2x01_P4.20mm_Vertical","Module 8 50 V drain feed",""
"26","J19","1","12V IN","Connector_Molex:Molex_Mini-Fit_Jr_5566-02A_2x01_P4.20mm_Vertical","12 V aux from subarray supply",""
"27","R1-R8","8","33","Resistor_SMD:R_0603_1608Metric","TX_EN source termination",""
